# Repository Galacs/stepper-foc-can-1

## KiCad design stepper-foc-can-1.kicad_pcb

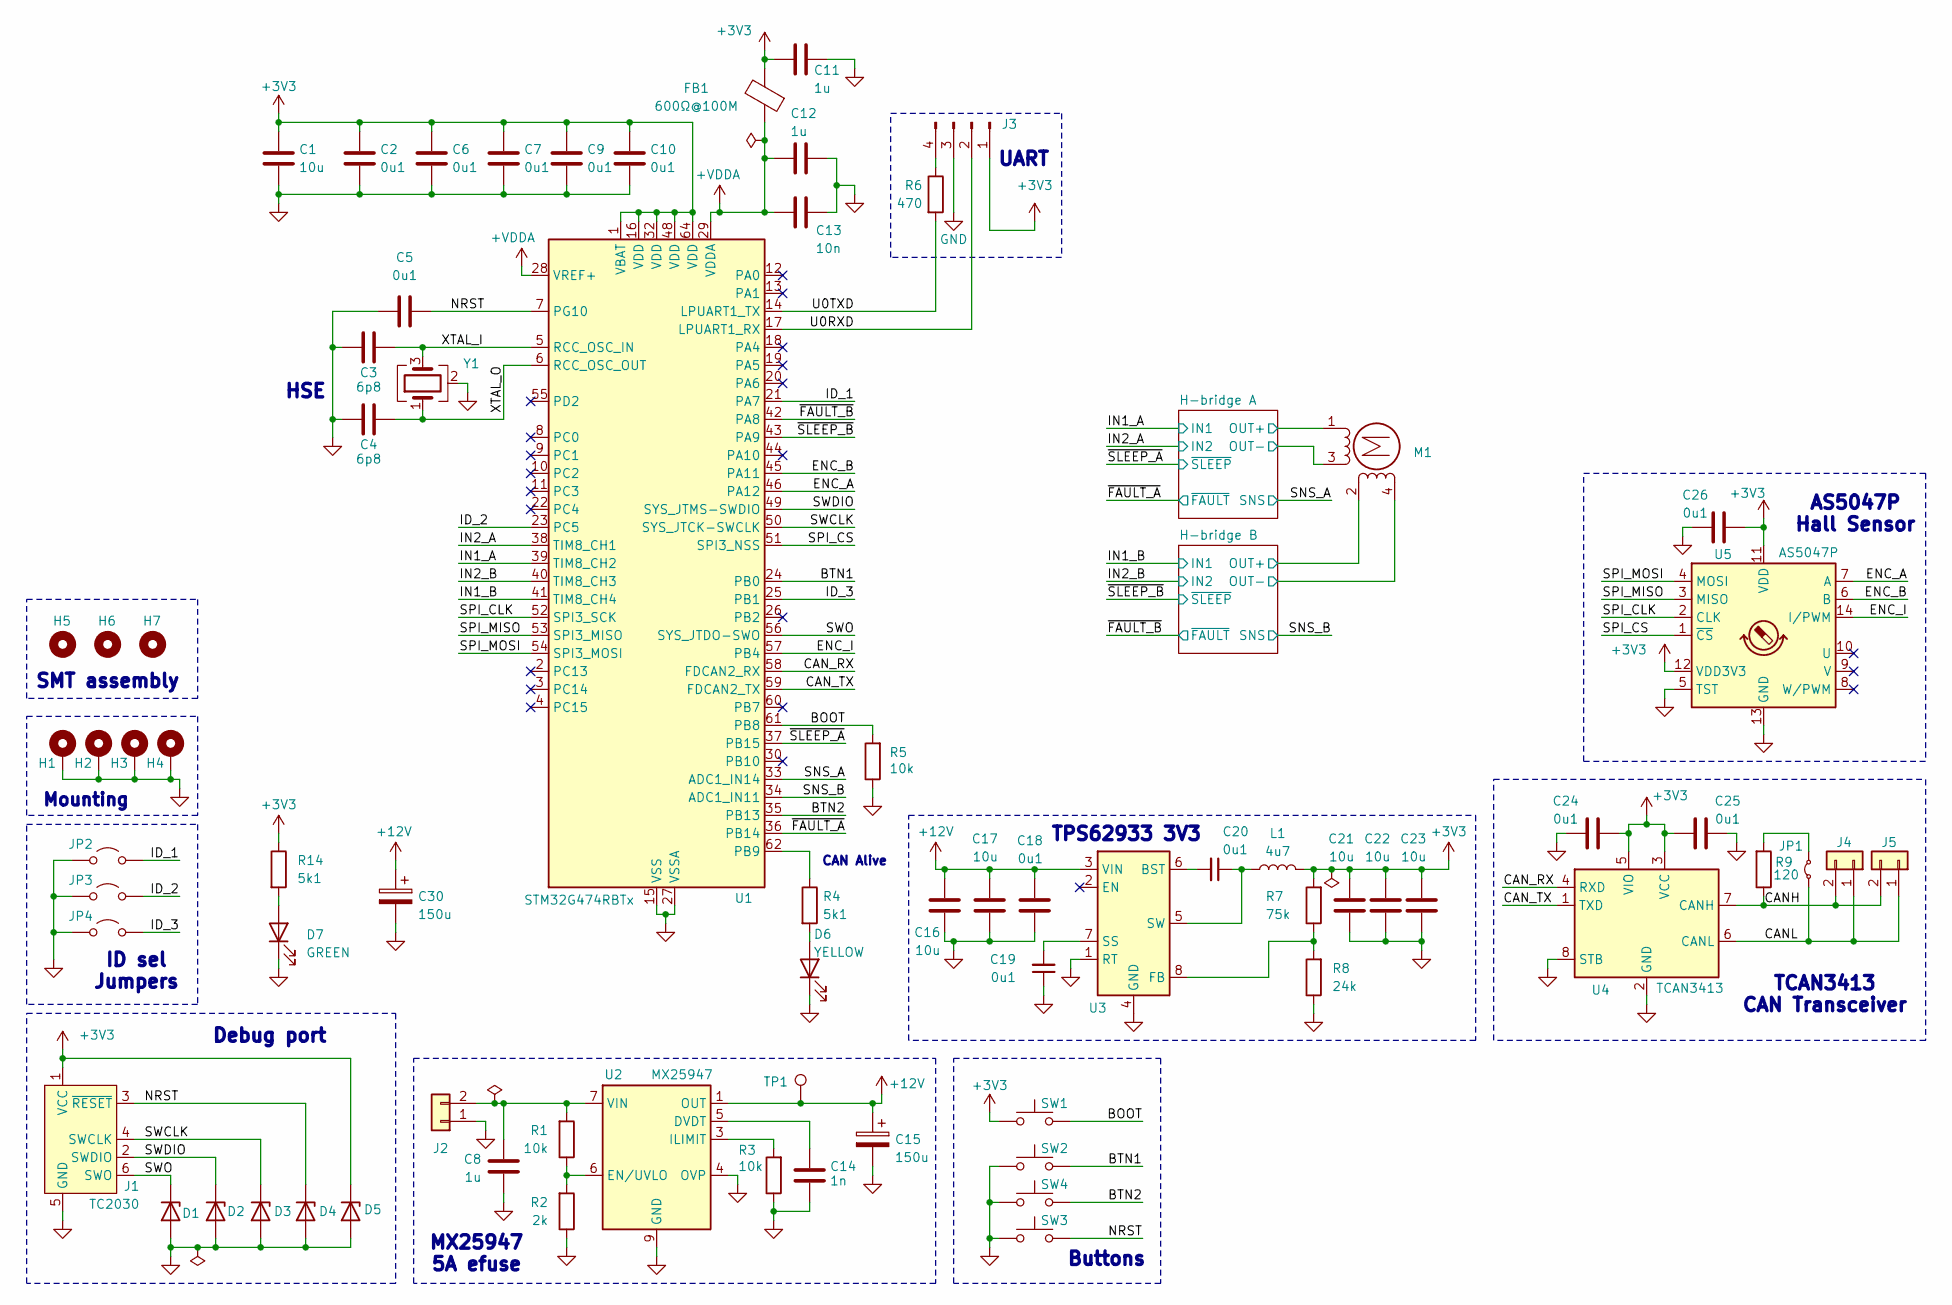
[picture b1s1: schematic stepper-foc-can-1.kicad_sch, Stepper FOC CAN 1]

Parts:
C1, C16, C17, C21, C22, C23: 10u; C_0805_2012Metric; Manufacturer Part Number GRM21BR61H106KE43L; JLCPCB Part # C440198
C2, C5, C6, C7, C9, C10, C18, C19, C20, C24, C25, C26: 0u1; C_0402_1005Metric; Manufacturer Part Number CL05B104KB54PNC; JLCPCB Part # C307331
C3, C4: 6p8; C_0603_1608Metric; Manufacturer Part Number 0402CG6R8C500NT; JLCPCB Part # C1576
C8, C11, C12: 1u; C_0402_1005Metric; Manufacturer Part Number CL05A105KA5NQNC; JLCPCB Part # C52923
C13: 10n; C_0402_1005Metric; Manufacturer Part Number CL05B103KB5NNNC; JLCPCB Part # C15195
C14: 1n; C_0402_1005Metric; Manufacturer Part Number 0402B102K500NT; JLCPCB Part # C1523
C15, C30: 150u; CP_Elec_6.3x7.7; Manufacturer Part Number EEEFTV151XAP; JLCPCB Part # C178603
D1, D2, D3, D4, D5: H5VU10U; Diode_DFN1006; Manufacturer Part Number H5VU10U; JLCPCB Part # C22395519
D6: YELLOW; LED_0805_2012Metric; Manufacturer Part Number KT-0805Y; JLCPCB Part # C2296
D7: GREEN; LED_0805_2012Metric; Manufacturer Part Number KT-0805G; JLCPCB Part # C2297
FB1: 600Ω@100M; L_0805_2012Metric; Manufacturer Part Number MPZ2012S601ATD25; JLCPCB Part # C81034
H1, H2, H3, H4: MountingHole_Pad; MountingHole_3.2mm_M3_ISO7380_Pad
H5, H6, H7: MountingHole; ToolingHole_1.152mm
J1: TC2030; Tag-Connect_TC2030-IDC-NL_2x03_P1.27mm_Vertical
J2, J4, J5: Conn_01x02; JST_XH_B2B-XH-A_1x02_P2.50mm_Vertical; Manufacturer Part Number B2B-XH-A(LF)(SN); JLCPCB Part # C158012
J3: Conn_01x04_Pin; PinHeader_1x04_P2.54mm_Horizontal
JP1: Jumper_2_Small_Bridged; PinHeader_1x02_P2.54mm_Horizontal
JP2, JP3, JP4: Jumper_2_Open; SolderJumper-2_P1.3mm_Open_RoundedPad1.0x1.5mm
L1: 4u7; L_1008_2520Metric; Manufacturer Part Number FTC252010S4R7MBCA; JLCPCB Part # C5832360
M1: Stepper_Motor_bipolar; JST_XH_S4B-XH-A_1x04_P2.50mm_Horizontal
R1, R3, R5: 10k; R_0402_1005Metric; Manufacturer Part Number 0402WGF1002TCE; JLCPCB Part # C25744
R2: 2k; R_0402_1005Metric; Manufacturer Part Number 0402WGF2001TCE; JLCPCB Part # C4109
R4, R14: 5k1; R_0402_1005Metric; Manufacturer Part Number 0402WGF5101TCE; JLCPCB Part # C25905
R6: 470; R_0402_1005Metric; Manufacturer Part Number 0402WGF4700TCE; JLCPCB Part # C25117
R7: 75k; R_0402_1005Metric; Manufacturer Part Number 0402WGF7502TCE; JLCPCB Part # C25798
R8: 24k; R_0402_1005Metric; Manufacturer Part Number 0402WGF2402TCE; JLCPCB Part # C25769
R9: 120; R_1206_3216Metric; Manufacturer Part Number 1206W4F1200T5E; JLCPCB Part # C17909
SW1, SW2, SW3, SW4: SW_Push; SW_SPST_TS-1088-xR020; Manufacturer Part Number TS-1088-AR02016; JLCPCB Part # C720477
TP1: TestPoint; TestPoint_Pad_D2.0mm
U1: STM32G474RBTx; LQFP-64_10x10mm_P0.5mm; Manufacturer Part Number STM32G474RBT3; JLCPCB Part # C1235414
U2: MX25947; TI_SO-PowerPAD-8_ThermalVias; Manufacturer Part Number MX25947ES; JLCPCB Part # C5875698
U3: TPS62933; SOT-583-8; Manufacturer Part Number TPS62933DRLR; JLCPCB Part # C3200405
U4: TCAN3413; TSOT-23-8; Manufacturer Part Number TCAN3413DDFR; JLCPCB Part # C30111221
U5: AS5047P; TSSOP-14_4.4x5mm_P0.65mm; Manufacturer Part Number AS5047P-ATSM; JLCPCB Part # C962063
Y1: Crystal_GND24; Crystal_SMD_2016-4Pin_2.0x1.6mm; Manufacturer Part Number XTM20024000DT00351001; JLCPCB Part # C37635325

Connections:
+3V3: C1.1, C2.1, C6.1, C7.1, C9.1, C10.1, C11.1, C21.1, C22.1, C23.1, C24.1, C25.1, C26.1, D5.1 (K), FB1.2, J1.1 (VCC), J3.1, L1.2, R7.2, R14.1, SW1.1, U1.1 (VBAT), U1.16 (VDD), U1.32 (VDD), U1.48 (VDD), U1.64 (VDD), U4.3 (VCC), U4.5 (VIO), U5.11 (VDD), U5.12 (VDD3V3); also elsewhere on the board
+12V: C15.1, C16.1, C17.1, C18.1, C30.1, TP1.1 (1_1), U2.1 (OUT), U2.2 (OUT), U3.3 (VIN); also elsewhere on the board
+VDDA: C12.1, C13.1, FB1.1, U1.28 (VREF+), U1.29 (VDDA); also elsewhere on the board
/BOOT: R5.2, SW1.2, U1.61 (PB8)
/BTN1: SW2.2, U1.24 (PB0)
/BTN2: SW4.2, U1.35 (PB13)
/CANH: J4.2, J5.2, R9.1, U4.7 (CANH)
/CANL: J4.1, J5.1, JP1.1 (A), U4.6 (CANL)
/CAN_RX: U1.58 (FDCAN2_RX), U4.4 (RXD)
/CAN_TX: U1.59 (FDCAN2_TX), U4.1 (TXD)
/ENC_A: U1.46 (PA12), U5.7 (A)
/ENC_B: U1.45 (PA11), U5.6 (B)
/ENC_I: U1.57 (PB4), U5.14 (I/PWM)
/H-bridge A/OUT+: M1.1 (-_1); also elsewhere on the board
/H-bridge A/OUT-: M1.3; also elsewhere on the board
/H-bridge B/OUT+: M1.2; also elsewhere on the board
/H-bridge B/OUT-: M1.4; also elsewhere on the board
/ID_1: JP2.2 (B), U1.21 (PA7)
/ID_2: JP3.2 (B), U1.23 (PC5)
/ID_3: JP4.2 (B), U1.25 (PB1)
/IN1_A: U1.39 (TIM8_CH2); also elsewhere on the board
/IN1_B: U1.41 (TIM8_CH4); also elsewhere on the board
/IN2_A: U1.38 (TIM8_CH1); also elsewhere on the board
/IN2_B: U1.40 (TIM8_CH3); also elsewhere on the board
/NRST: C5.2, D4.1 (K), J1.3 (~RESET), SW3.2, U1.7 (PG10)
/SNS_A: U1.33 (ADC1_IN14); also elsewhere on the board
/SNS_B: U1.34 (ADC1_IN11); also elsewhere on the board
/SPI_CLK: U1.52 (SPI3_SCK), U5.2 (CLK)
/SPI_CS: U1.51 (SPI3_NSS), U5.1 (~CS)
/SPI_MISO: U1.53 (SPI3_MISO), U5.3 (MISO)
/SPI_MOSI: U1.54 (SPI3_MOSI), U5.4 (MOSI)
/SWCLK: D3.1 (K), J1.4 (SWCLK), U1.50 (SYS_JTCK-SWCLK)
/SWDIO: D2.1 (K), J1.2 (SWDIO), U1.49 (SYS_JTMS-SWDIO)
/SWO: D1.1 (K), J1.6 (SWO), U1.56 (SYS_JTDO-SWO)
/U0RXD: J3.2, U1.17 (LPUART1_RX)
/U0TXD: R6.2, U1.14 (LPUART1_TX)
/XTAL_I: C3.1, U1.5 (RCC_OSC_IN), Y1.3
/XTAL_O: C4.1, U1.6 (RCC_OSC_OUT), Y1.1
/~FAULT_A: U1.36 (PB14); also elsewhere on the board
/~FAULT_B: U1.42 (PA8); also elsewhere on the board
/~SLEEP_A: U1.37 (PB15); also elsewhere on the board
/~SLEEP_B: U1.43 (PA9); also elsewhere on the board
GND: C1.2, C2.2, C3.2, C4.2, C5.1, C6.2, C7.2, C8.1, C9.2, C10.2, C11.2, C12.2, C13.2, C14.2, C15.2, C16.2, C17.2, C18.2, C19.1, C21.2, C22.2, C23.2, C24.2, C25.2, C26.2, C30.2, D1.2 (A), D2.2 (A), D3.2 (A), D4.2 (A), D5.2 (A), D6.1 (K), D7.1 (K), H1.1 (1_1), H2.1 (1_1), H3.1 (1_1), H4.1 (1_1), J1.5 (GND), J2.1, J3.3, JP2.1 (A), JP3.1 (A), JP4.1 (A), R2.1, R3.1, R5.1, R8.1, SW2.1, SW3.1, SW4.1, U1.15 (VSS), U1.27 (VSSA), U1.31 (VSS), U1.47 (VSS), U1.63 (VSS), U2.4 (OVP), U2.9 (GND), U3.1 (RT), U3.4 (GND), U4.2 (GND), U4.8 (STB), U5.5 (TST), U5.13 (GND), Y1.2 (G), Y1.4 (G); also elsewhere on the board
unnamed: D6.2 (A), R4.2
unnamed: D7.2 (A), R14.2
unnamed: J3.4, R6.1
unnamed: JP1.2 (B), R9.2
unnamed: R4.1, U1.62 (PB9)
unnamed: C14.1, U2.5 (DVDT)
unnamed: R1.1, R2.2, U2.6 (EN/UVLO)
unnamed: R3.2, U2.3 (ILIMIT)
unnamed: C20.2, U3.6 (BST)
unnamed: R7.1, R8.2, U3.8 (FB)
unnamed: C19.2, U3.7 (SS)
unnamed: C20.1, L1.1, U3.5 (SW)
VIN: C8.2, J2.2, R1.2, U2.7 (VIN), U2.8 (VIN)

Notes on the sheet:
Mounting
AS5047P Hall Sensor
TPS62933 3V3
CAN Alive
UART
MX25947 5A efuse
SMT assembly
HSE
TCAN3413 CAN Transceiver
Buttons
Debug port
ID sel Jumpers

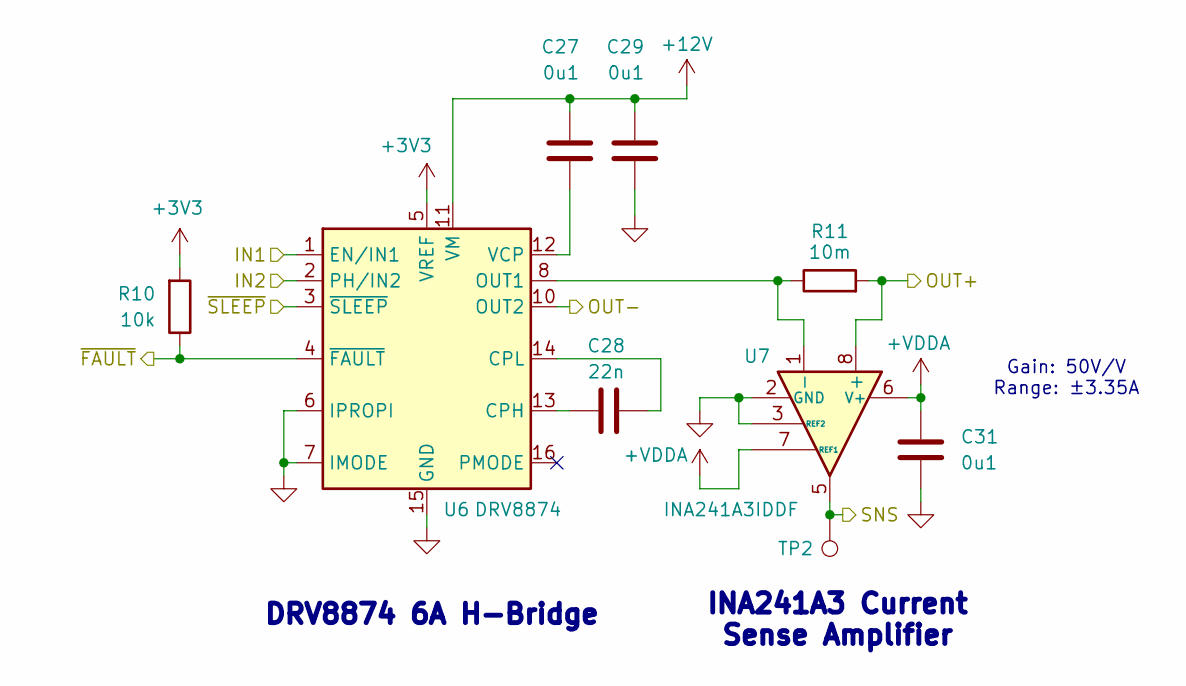
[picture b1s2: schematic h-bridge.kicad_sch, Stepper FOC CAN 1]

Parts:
C27, C29, C31: 0u1; C_0402_1005Metric; Manufacturer Part Number CL05B104KB54PNC; JLCPCB Part # C307331
C28: 22n; C_0402_1005Metric; Manufacturer Part Number 0402B223K500NT; JLCPCB Part # C1532
R10: 10k; R_0402_1005Metric; Manufacturer Part Number 0402WGF1002TCE; JLCPCB Part # C25744
R11: 10m; R_0805_2012Metric; Manufacturer Part Number HoYLR0805-1/2W-10mR-1%; JLCPCB Part # C22450688
TP2: TestPoint; TestPoint_Pad_D2.0mm
U6: DRV8874; HTSSOP-16-1EP_4.4x5mm_P0.65mm_EP3.4x5mm_Mask2.46x2.31mm_The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; Manufacturer Part Number DRV8874PWPR; JLCPCB Part # C1855818
U7: INA241A3IDDF; SOT-23-8; Manufacturer Part Number INA241A3IDDFR; JLCPCB Part # C6051860

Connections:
+3V3: R10.2, U6.5 (VREF); also elsewhere on the board
+12V: C27.1, C29.1, U6.11 (VM); also elsewhere on the board
+VDDA: C31.1, U7.6 (V+), U7.7 (REF1); also elsewhere on the board
/H-bridge A/OUT+: R11.2, U7.8 (+); also elsewhere on the board
/H-bridge A/OUT-: U6.10 (OUT2); also elsewhere on the board
/IN1_A: U6.1 (EN/IN1); also elsewhere on the board
/IN2_A: U6.2 (PH/IN2); also elsewhere on the board
/SNS_A: TP2.1 (1_1), U7.5; also elsewhere on the board
/~FAULT_A: R10.1, U6.4 (~FAULT); also elsewhere on the board
/~SLEEP_A: U6.3 (~SLEEP); also elsewhere on the board
GND: C29.2, C31.2, U6.6 (IPROPI), U6.7 (IMODE), U6.9 (PGND), U6.15 (GND), U6.17 (EPAD), U7.2 (GND), U7.3 (REF2), U7.4 (GND); also elsewhere on the board
unnamed: C28.1, U6.13 (CPH)
unnamed: C28.2, U6.14 (CPL)
unnamed: R11.1, U6.8 (OUT1), U7.1 (-)
unnamed: C27.2, U6.12 (VCP)

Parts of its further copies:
C32, C34, C36: 0u1; C_0402_1005Metric; Manufacturer Part Number CL05B104KB54PNC; JLCPCB Part # C307331
C33: 22n; C_0402_1005Metric; Manufacturer Part Number 0402B223K500NT; JLCPCB Part # C1532
R12: 10k; R_0402_1005Metric; Manufacturer Part Number 0402WGF1002TCE; JLCPCB Part # C25744
R13: 10m; R_0805_2012Metric; Manufacturer Part Number HoYLR0805-1/2W-10mR-1%; JLCPCB Part # C22450688
TP3: TestPoint; TestPoint_Pad_D2.0mm
U8: DRV8874; HTSSOP-16-1EP_4.4x5mm_P0.65mm_EP3.4x5mm_Mask2.46x2.31mm_The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; Manufacturer Part Number DRV8874PWPR; JLCPCB Part # C1855818
U9: INA241A3IDDF; SOT-23-8; Manufacturer Part Number INA241A3IDDFR; JLCPCB Part # C6051860

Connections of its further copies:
+3V3: R12.2, U8.5 (VREF); also elsewhere on the board
+12V: C32.1, C34.1, U8.11 (VM); also elsewhere on the board
+VDDA: C36.1, U9.6 (V+), U9.7 (REF1); also elsewhere on the board
/H-bridge B/OUT+: R13.2, U9.8 (+); also elsewhere on the board
/H-bridge B/OUT-: U8.10 (OUT2); also elsewhere on the board
/IN1_B: U8.1 (EN/IN1); also elsewhere on the board
/IN2_B: U8.2 (PH/IN2); also elsewhere on the board
/SNS_B: TP3.1 (1_1), U9.5; also elsewhere on the board
/~FAULT_B: R12.1, U8.4 (~FAULT); also elsewhere on the board
/~SLEEP_B: U8.3 (~SLEEP); also elsewhere on the board
GND: C34.2, C36.2, U8.6 (IPROPI), U8.7 (IMODE), U8.9 (PGND), U8.15 (GND), U8.17 (EPAD), U9.2 (GND), U9.3 (REF2), U9.4 (GND); also elsewhere on the board
unnamed: C33.1, U8.13 (CPH)
unnamed: C33.2, U8.14 (CPL)
unnamed: R13.1, U8.8 (OUT1), U9.1 (-)
unnamed: C32.2, U8.12 (VCP)

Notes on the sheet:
Gain: 50V/V Range: ±3.35A
INA241A3 Current Sense Amplifier
DRV8874 6A H-Bridge

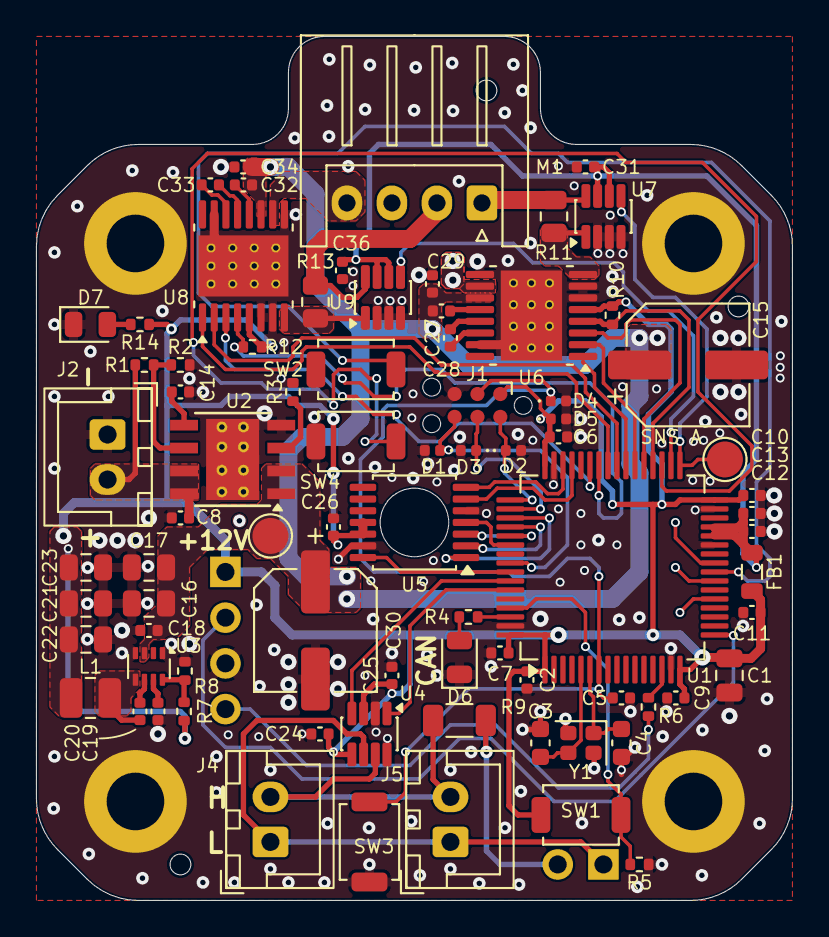
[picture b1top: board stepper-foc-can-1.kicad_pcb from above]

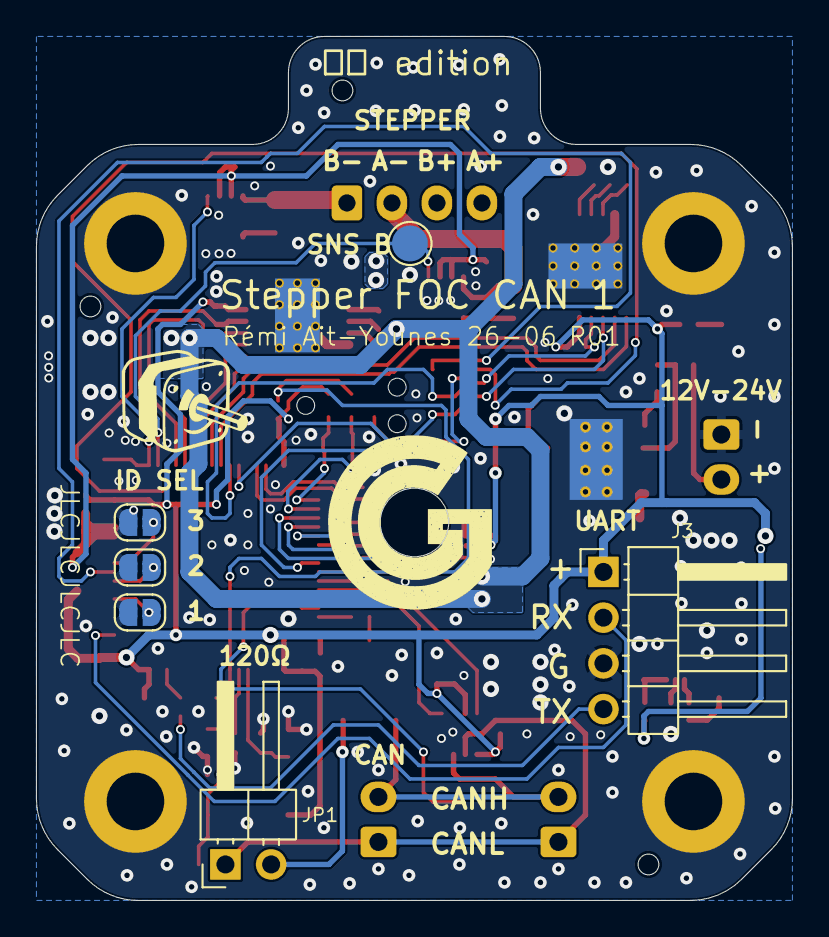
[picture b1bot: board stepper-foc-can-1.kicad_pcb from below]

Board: 4 copper layers, 42.0 x 48.0 mm, 92 parts (6 on the bottom side), 64 nets.

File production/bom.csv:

Designator,Footprint,Quantity,Value,LCSC Part #
"C1, C16, C17, C21, C22, C23",0805,6,10u,C440198
"C10, C18, C19, C2, C20, C24, C25, C26, C27, C29, C31, C32, C34, C36, C5, C6, C7, C9",0402,18,0u1,C307331
"C11, C12, C8",0402,3,1u,C52923
C13,0402,1,10n,C15195
C14,0402,1,1n,C1523
"C15, C30",CP_Elec_6.3x7.7,2,150u,C178603
"C28, C33",0402,2,22n,C1532
"C3, C4",0603,2,6p8,C1576
"D1, D2, D3, D4, D5",Diode_DFN1006,5,H5VU10U,C22395519
D6,0805,1,YELLOW,C2296
D7,0805,1,GREEN,C2297
FB1,0805,1,600Ω@100M,C81034
"JP2, JP3, JP4",SolderJumper-2_P1.3mm_Open_RoundedPad1.0x1.5mm,3,Jumper_2_Open,
L1,1008,1,4u7,C5832360
"R1, R10, R12, R3, R5",0402,5,10k,C25744
"R11, R13",0805,2,10m,C22450688
"R14, R4",0402,2,5k1,C25905
R2,0402,1,2k,C4109
R6,0402,1,470,C25117
R7,0402,1,75k,C25798
R8,0402,1,24k,C25769
R9,1206,1,120,C17909
"SW1, SW2, SW3, SW4",SW_SPST_TS-1088-xR020,4,SW_Push,C720477
U1,LQFP-64_10x10mm_P0.5mm,1,STM32G474RBTx,C1235414
U2,TI_SO-PowerPAD-8_ThermalVias,1,MX25947,C5875698
U3,SOT-583-8,1,TPS62933,C3200405
U4,TSOT-23-8,1,TCAN3413,C30111221
U5,TSSOP-14_4.4x5mm_P0.65mm,1,AS5047P,C962063
"U6, U8",HTSSOP-16-1EP_4.4x5mm_P0.65mm_EP3.4x5mm_Mask2.46x2.31mm_ThermalVias,2,DRV8874,C1855818
"U7, U9",SOT-23-8,2,INA241A3IDDF,C6051860
Y1,Crystal_SMD_2016-4Pin_2.0x1.6mm,1,Crystal_GND24,C37635325

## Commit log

2026-06-29 schem: add stm32g474
2026-06-29 schem: add stm32 decoupling caps
2026-06-29 schem: add hse and reset
2026-06-29 schem: add boot
2026-06-29 schem: add tc2030 swd connector
2026-06-29 schem: add MX25947 5A efuse
2026-06-29 schem: add uart connctor
2026-06-29 schem: fix uart pins
2026-06-29 schem: import TCAN3413 CAN Transceiver
2026-06-29 schem: add btns
2026-06-29 schem: add TPS62933 3V3 buck
2026-06-29 schem: add AS5047P Hall Sensor
2026-06-29 schem: add can led
2026-06-29 schem: add DRV8874 h bridge driver
2026-06-29 schem: add INA241A ultra precision current sense amp
2026-06-29 schem: add second h bridge and motor connector
2026-06-29 schem: connect h bridges to mcu
2026-06-29 schem: add no connects
2026-06-29 schem: run and fix ERC
2026-06-29 schem: add net classes
2026-06-29 schem: add missing footprints
2026-06-29 schem: add ordering info to BOM
2026-06-29 schem: add title
2026-06-29 schem: reannotate
2026-06-29 schem: add mounting holes
2026-06-29 pcb: import jlc 4 layer stackup
2026-06-29 pcb: import footprints from schem
2026-06-29 pcb: fix missing 3d models
2026-06-29 pcb: add board outline
2026-06-29 pcb: add can layout
2026-06-29 pcb: add hall sensor layout
2026-06-29 pcb: add efuse layout
2026-06-29 pcb: add smps layout
2026-06-29 pcb: add stm32 layout
2026-06-29 schem: update 22n capacitor PN
2026-06-29 pcb: add stepper drvs layout
2026-06-29 schem: update mounting holes footprint
2026-06-29 pcb: add drvs placement
2026-06-29 pcb: add stm32 placement
2026-06-30 schem/pcb: fix caps
2026-06-30 schem/pcb: add tooling holes
2026-06-30 pcb: add gnd planes
2026-06-30 pcb: add gnd vias
2026-06-30 pcb: add drill/place origin
2026-06-30 schem: reorganize programmable gpios
2026-06-30 pcb: add xtal routing
2026-06-30 pcb: add SPI routing
2026-06-30 pcb: add can routing
2026-06-30 pcb: add pwm routing
2026-06-30 pcb: route analog current sense
2026-06-30 pcb: add swd routing
2026-06-30 pcb: route encoder
2026-06-30 pcb: add efuse routing
2026-06-30 pcb: add smps routing
2026-06-30 pcb: add +12v and drvs routing
2026-06-30 pcb: add drv sleep/fault routing
2026-06-30 pcb: add +3v3 pwr routing
2026-06-30 pcb: route vref
2026-06-30 pcb: route nrst
2026-06-30 schem: add id selection jumpers 3bit
2026-06-30 pcb: route id jumpers
2026-06-30 pcb: add uart routing
2026-06-30 pcb: add painful btns routing
2026-06-30 pcb: route missing +12v
2026-06-30 pcb: add stitching vias
2026-06-30 pcb: run and fix DRC
2026-06-30 pcb: remove unused internal pads
2026-06-30 pcb(silk): clean reference designators
2026-06-30 schem: add +3v3 status led
2026-06-30 pcb(silk): add user txt
2026-06-30 pcb: add title
2026-06-30 generate production files
